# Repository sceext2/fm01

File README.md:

<!-- lang: zh_CN -->
<!-- fm01-2020/fm01_doc -->

# fm01_doc
<https://github.com/fm01-2020/fm01_doc>

胖蚊子 (Fat Mosquito) 系列文档.

胖蚊子系列起源于胖蚊子 1 号 (FM01) 小飞机, 但在制造小飞机的过程中,
相关技术产生了更多项目.
现将所有项目统称为胖蚊子系列, 并将相关文档集中于 `fm01_doc`.

(胖蚊子: 白天休息, 晚上出来嗡嗡嗡 ~ )

注: 目前大部分这些项目都处于起步阶段.

## 已完成的项目

| 代号 (code) | 名称 (name) | 说明 | 成本 (CNY) | 备注 | 完成时间 |
| :--------- | :---------- | :--- | --------: | :--- | :------: |
| [LQFP64-10x10mm-CLAMP](./kicad/lqfp64-10x10mm-clamp) | LQFP64 芯片夹座 | 用于免焊接测试单片机 | 1 | | 2020 |

注: 成本仅供参考.

## 进行中的项目 (2021)

| 代号 (code) | 名称 (name) | 说明 | 成本 (CNY) | 备注 |
| :--------- | :---------- | :--- | --------: | :--- |
| FMUV-2 | 胖蚊子紫外线强度计 | 作为一个精美小礼物 | (100) | |
| FMLHR-1 | 胖蚊子光除毛 | 810nm 近红外光脉冲除毛 | (400) | |
| fmprinter-1 | 胖蚊子打印机 | 简单的廉价小型打印机 | (30) | |
| FMOS-2 | 胖蚊子示波器 FPGA 版 (USB 2.0) | 50Msps 6bit, 30Msps 10bit | (100) | 2022 |
| FMUPS-1 | 胖蚊子电源 | 12V 600W, 降压开关电源, 电池充电器, 逆变器, UPS, 多机并联同步 | (100) | 2022 |
| FMUPS-1-B | FMUPS-1 电池包 | 21700 锂电池, 16.8V, 250W 4h (1kWh) | (500) | 2022 |
| FMSB-1 | 胖蚊子微派 1 | SBC: 全志 A20 SoC | (100) | 2022 |
| FMSB-2 | 胖蚊子微派 2 | SBC: 全志 V3 SoC | (100) | 2022 |
| FMSB-3 | 胖蚊子微派 3 | SBC: 全志 V3s SoC | (100) | 2022 |

注: 成本仅供参考.

## 重要目录

| 目录 | 说明 |
| :--: | :-- |
| [kicad](./kicad) | 胖蚊子系列 PCB |
| [fmp](./fmp) | 胖蚊子系列使用的通信协议 (protocol) |
| [libfm-rs](./libfm-rs) | 胖蚊子系列软件库: 胖蚊子系列是软硬件混合的项目, 硬件需要软件的驱动 |

## 胖蚊子系列设计原则 (6)

+ **廉价**.

  在设计性能可以接受的情况下 (不追求高性能), 尽可能使用廉价的设计与硬件选型, 避免使用昂贵的模块, 组件, 芯片, 元器件.
  追求胖蚊子系列整体的硬件低成本.
  避免因为过高的价格, 而阻止更多人尝试胖蚊子系列.

+ **原料易得**.

  胖蚊子系列的硬件模块, 组件, 元器件等的选型, 以及组装所需使用的各种工具, 应使用方便购买, 货源充足的.
  使用常见的标准, 接口.
  避免因为买不到相应的硬件材料, 而阻止更多人尝试胖蚊子系列.

+ **一致性**.

  胖蚊子系列尽可能共用同样的技术, 模块, 接口, 器件选型, 协议, 工具, 使用同样的设计风格.

+ **数字化与安全性**.

  在胖蚊子系列的各硬件模块之间, 各设备之间, 尽量使用数字通信协议, 不使用模拟通信协议.
  通信协议考虑加密, 完整性, 干扰等安全性因素.
  胖蚊子系列的软硬件设计, 考虑冗余, 模块故障或失效的处理, 应急策略等多种安全机制.
  尽可能避免或减少机器伤人.

  胖蚊子系列的软件部分, 尽可能避免或减少使用 C 语言.
  尽量使用 [rust](https://www.rust-lang.org/) 编程语言, 以提高软件部分的稳定性与安全性.

+ **开源**.

  胖蚊子系列的所有软件代码与硬件设计全部开源, 并尽可能丰富文档内容.
  以便更多人尝试胖蚊子系列.

+ **高级用户界面与机器接口相分离**.

  胖蚊子系列的 **高级用户界面** (图形, 数字, 复杂操作控制, 多媒体等) 全部位于上位机 (PC 或手机).
  MCU 不涉及高级用户界面, 只提供上位机接口 (fmp).

  机器本身 (MCU 侧) 最多只有非常简单的 **低级用户界面** (电源开关, 状态指示灯, 急停按钮).

  尽量分离用户界面和机器接口, 可以方便机器之间的互联协调配合.
  尽量使用机器去控制机器, 把人解放出来.

## LICENSE

[`CC-BY-SA 4.0+`](https://creativecommons.org/licenses/by-sa/4.0/)

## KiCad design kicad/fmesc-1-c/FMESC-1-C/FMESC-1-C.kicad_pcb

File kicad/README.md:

# fm01_doc/kicad
胖蚊子系列 PCB, 使用设计工具 [KiCad](https://kicad-pcb.org/).

## 经过测试验证的电路板

这些 PCB 经过制造, 并测试成功, 达到了设计的预期效果.

| 序号 | 名称 | 说明 | 规格 | 建议颜色 | 版本号 | 成本 (CNY) | 备注 |
| :--: | :-- | :--- | :--- | :-----: | :---- | ---------: | :-- |
| 1 | [`LQFP64-10x10mm-CLAMP`](./lqfp64-10x10mm-clamp) | LQFP64, LQFP48 芯片夹座, 用于免焊接烧录单片机 | 25x25mm 大小 (x3), 1.6mm 厚度, 2 层, FR-4 | 绿 | v0.1 2020-11-15 | 1.0 | |

注: 成本仅供参考.

## 设计中的电路板

这些 PCB 还没有通过测试, 或者还没有制造过, 或者还在设计中.

| 序号 | 名称 | 说明 | 规格 | 建议颜色 | 版本号 | 成本 (CNY) | 备注 |
| :--: | :-- | :--- | :--- | :-----: | :---- | ---------: | :-- |
| 1 | FMPCBVDL-1 | PCB 垂直连接器 (2P, 1.4x2.8mm) | 4x16mm 大小, 1.6mm 厚度, 2 层, FR-4 | 黄 | v0.1 2020-11-29 | 1 | |
| 2 | `FMESC-1-A` | 胖蚊子电调 (FMESC-1) 底层大板 | 48x48mm (48x54mm) 大小, 1.6mm 厚度, 1 层, 铝基 或 FR-4, 24x48mm (M2) 孔距 | 黄 (FR-4), 白 (铝基) | v0.3 2020-11-29 | 18 | |
| 3 | FMESC-1-C | 胖蚊子电调 (FMESC-1) MOS 驱动小板 | 12x20mm 大小, 1.0mm 厚度, 2 层, FR-4 | 蓝 | | 4 | |
| 4 | FMSMD-2 | 步进电机驱动 (4 路), 使用 HR8833MTE (1.5A, 2 细分) | 20x50mm 大小, 1.6mm 厚度, 2 层, FR-4 | 黄 | | 10 | |

## 计划中及设计早期的电路板

这些 PCB 还在设计早期阶段, 或者只是计划中.

| 序号 | 名称 | 说明 | 规格 | 建议颜色 | 版本号 | 成本 (CNY) | 备注 |
| :--: | :-- | :--- | :--- | :-----: | :---- | ---------: | :-- |
| 1 | FMC-1-SF0RC | 胖蚊子主控板 (stm32f030rct6 芯片) | 20x40mm 大小, 1.0mm 厚度, 2 层, FR-4 | 绿 | | 10 | |
| 2 | FMC-1-SF1RE | 胖蚊子主控板 (stm32f103ret6 芯片) | 20x40mm 大小, 1.0mm 厚度, 2 层, FR-4 | 绿 | | 10 | |
| 3 | FM02-B-1 | 胖蚊子 2 号 (FM02) 机架及主要电路板 | 100x100mm 大小, 1.6mm 厚度, 2 层, FR-4 | 黄 | | 10 | |
| 4 | FM01-ES2-1 | 胖蚊子 1 号 (FM01) 承载 esp32-s2 wrover-i 模块的小板 | 20x32mm 大小, 1.0mm 厚度, 2 层, FR-4 | 绿 | | | |

## 胖蚊子系列 PCB 阻焊颜色使用说明

可选颜色 (JLC): `绿`, `红`, `黄`, `蓝`, `白`, `黑` (6 种).

保留颜色 (尽量不使用): `红`, `黑` (2 种).

1. **普通板** (未分类, 默认颜色): `绿` (FR-4, 厚 1.6mm, 1.0mm).

  比如: `LQFP64-10x10mm-CLAMP`

2. **主控板** (单片机 stm32, esp32 等): `绿` (FR-4, 厚 1.0mm).

  比如: `FMC-1-SF0RC`, `FMC-1-SF1RE`, `FM01-ES2-1`

3. **功率板** (电机驱动板, 电源板), **机架**: `黄` (FR-4, 厚 1.6mm).

  比如: `FMESC-1-A`, `FMSMD-2`, `FM02-B-1`

4. **铝基板**: `白` (铝基, 厚 1.6mm, 1.0mm).

5. **特殊板** (飞线板, 4 层板): `蓝` (FR-4, 厚 1.0mm).

  比如: `FMESC-1-C`

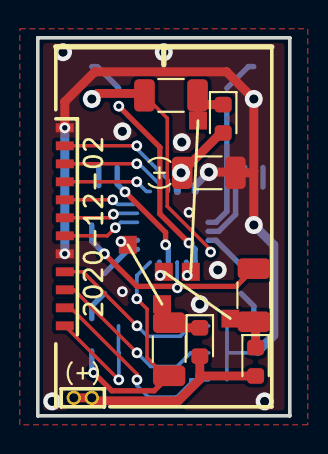
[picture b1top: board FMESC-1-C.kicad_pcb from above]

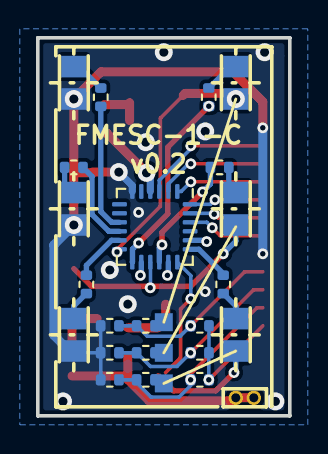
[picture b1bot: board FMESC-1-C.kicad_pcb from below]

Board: 2 copper layers, 14.0 x 21.0 mm, 40 parts (25 on the bottom side), 36 nets.

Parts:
C0, C1, C2, C3: 10u; C_1206_3216Metric
D1, D2, D3: D; D_0603_1608Metric
J1, J2, J3, J4, J5, J6: Conn_01x02; FMPCBVDL-1-S
JA2: Conn_01x01; JS_1P_1x1mm
JB2: Conn_01x01; JS_1P_1x1mm
JC2: Conn_01x01; JS_1P_1x1mm
JM1: Conn_01x12; JS_12P_1.0mm
JP1: Conn_01x02; JT_2P_1.0mm
JV1, JV2, JV3, JV4, JV5, JV6: Conn_01x01; JS_1P_1x1mm
R1, R2, R3, R4, R5, R6: 10; R_0402_1005Metric
R11, R13, R15, R21, R22, R23: 2k; R_0402_1005Metric
R12, R14, R16: 20k; R_0402_1005Metric
U1: FD6288Q; QFN-24-1EP_4x4mm_P0.5mm_EP2.7x2.7mm_nopad

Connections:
+BATT: C0.2, D1.2, D2.2, D3.2, JP1.1, JP1.2, U1.4
/A1: C1.2, J2.1, U1.18
/AHG: R2.1, U1.19
/ALG: R1.1, U1.11
/B1: C2.2, J4.1, U1.15
/BHG: R4.1, U1.16
/BLG: R3.1, U1.10
/C1: C3.2, J6.1, U1.12
/CHG: R6.1, U1.13
/CLG: R5.1, U1.9
/GHA: JM1.7, U1.22
/GHB: JM1.6, U1.23
/GHC: JM1.5, U1.24
/GLA: JM1.4, U1.1
/GLB: JM1.3, U1.2
/GLC: JM1.2, U1.3
/S0: JM1.12, R21.1, R22.1, R23.1
/SA: JM1.11, R11.2, R12.1, R21.2
/SB: JM1.10, R13.2, R14.1, R22.2
/SC: JM1.9, R15.2, R16.1, R23.2
GND: C0.1, J1.1, J3.1, J5.1, JM1.1, JM1.8, R11.1, R13.1, R15.1, U1.6
unnamed: C1.1, D1.1, JV2.1
unnamed: C2.1, D2.1, JV4.1
unnamed: C3.1, D3.1, JV6.1
unnamed: J1.2, R1.2
unnamed: J2.2, R2.2
unnamed: J3.2, R3.2
unnamed: J4.2, R4.2
unnamed: J5.2, R5.2
unnamed: J6.2, R6.2
unnamed: JA2.1, R12.2
unnamed: JB2.1, R14.2
unnamed: JC2.1, R16.2
unnamed: JV1.1, U1.20
unnamed: JV3.1, U1.17
unnamed: JV5.1, U1.14

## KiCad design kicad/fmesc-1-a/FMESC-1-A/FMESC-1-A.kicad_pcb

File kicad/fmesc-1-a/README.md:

# FMESC-1-A

胖蚊子电调 (FMESC-1) 底层大版.
与 [FMESC-1-C](../fmesc-1-c/) 以及 `FMC-1` 主控板配合使用.

+ 设计电池电压: 2s ~ 4s  (6.6V ~ 16.8V)

+ 设计最大单路电流: 40A

## PCB 设计参数

| 序号 | 项目 | 数值 |
| :--: | :-- | ---: |
| 1 | PCB 大小 | 48x48mm (48x54mm) |
| 2 | 材质 | 铝基 厚度 1.6mm 铜箔厚度 1oz (35um) |
| 3 | 层数 | 1 (单面) |
| 4 | 最小线宽线距 | 0.16mm (6mil) |
| 5 | 最小过孔内径 | 0.3mm |
| 6 | 最小过孔外径 | 0.6mm |
| 7 | 最小字符高度 | 0.8mm |
| 8 | 最小过孔间距 | 0.4mm |
| 9 | 最小过孔与线间距 | 0.25mm |
| 10 | 最小非金属化槽宽度 | 0.8mm |

推荐加工厂: [捷配](https://www.jiepei.com/)

## 元件清单

| 序号 | 引用 | 型号 | 封装 | 数量 | 价格 (CNY) |
| :--: | :-- | :--- | :--: | --: | ---------: |
| 1 | `Q1`, `Q2`, `Q3`, `Q4`, `Q5`, `Q6`, `Q7`, `Q8`, `Q9`, `Q10`, `Q11`, `Q12`, `Q13`, `Q14`, `Q15`, `Q16`, `Q17`, `Q18`, `Q19`, `Q20`, `Q21`, `Q22`, `Q23`, `Q24` | AON6504 (NMOS 30V 85A 3.2mR) | DFN5x6 (6x5mm) | 24 | 0.7 x24 = 16.8 |
| 2 | `J1`, `J2`, `J3`, `J4`, `J5`, `J6`, `J7`, `J8`, `J9`, `J10`, `J11`, `J12`, `J13`, `J14`, `J15`, `J16`, `J17`, `J18`, `J19`, `J20`, `J21`, `J22`, `J23`, `J24`, `JT1`, `JT2`, `JT3` | FMPCBVDL-1 (2P, 1.4x2.8mm) | SMD | 27 | 1 |
| 总计 | 31 | 2 | 2 | 31 | 17.8 |

不在电路板上的额外元器件如下:

| 序号 | 型号 | 说明 | 数量 | 价格 (CNY) |
| :--: | :-- | :--- | ---: | ---------: |
| 1 | 电容 50V 470uF 铝电解 直插 | 并接在电源线入口处, 用于维持电调供电电压稳定 | 1 | 0.26 |
| 2 | 二极管 20A 1000V 直插 | (电路保护) 反向并接在电源线入口处, 用于防止电源正负极反接 | 1 | 0.4 |
| 3 | 压敏电阻 20D220K 22V 直插 | (电路保护) 并接在电源线入口处, 用于防止输入过高电压 | 1 | 0.68 |
| 总计 | 3 | | 3 | 1.4 |

注: 价格仅供参考.

## 接口引脚说明

| 序号 | 引用 | 说明 |
| :--: | :-- | :--- |
| 1 | `JG0`, `JG1` ~ `JG12` | GND 接电源负极 |
| 2 | `JB0`, `JB1` ~ `JB12` | VB 接电源正极 |
| 3 | `MA1`, `MB1`, `MC1` | 接 1 号无刷电机 |
| 4 | `MA2`, `MB2`, `MC2` | 接 2 号无刷电机 |
| 5 | `MA3`, `MB3`, `MC3` | 接 3 号无刷电机 |
| 6 | `MA4`, `MB4`, `MC4` | 接 4 号无刷电机 |
| 7 | `J1` ~ `J24` | 接上层电路板 `FMESC-1-C` |
| 8 | `JT1`, `JT2`, `JT3` | 接上层电路板 `FMC-1` |

## 功能电路

TODO

## 保护电路

胖蚊子小飞机整体电路保护方案请见 [电路保护](../../fm01/circuit_protect.md) 文档.

作为四合一电调, 胖蚊子电调 (`FMESC-1-A` 电路板) 在此处充当了主分电板的角色.
因此在电源入口处, 反向并接一只大电流大功率二极管, 用于防止电源正负极反接.
同时并接一只 22V 压敏电阻, 用于过压保护, 防止接入超过最大设计电压的电源.

注意在此种保护机制下, 如果发生电源接错 (反接, 过压) 则本电路板相当于直接短路, 会造成电源承担很大的电流.
此处的保护机制目的是保护本电路板, 以及其余的上级电路板 (比如飞控), 而不是保护电源.

因此, 此处的保护机制单独无法提供足够的安全性, 接入本电路板的电池组, 必须自身具有一定的保护机制, 能够对短路大电流做出反应.
建议的电池组保护机制, 详见上述 *电路保护* 文档, 即采用过流保护 (自恢复保险丝) 以及电池电源指示灯 (故障状态指示).

## 电路板装配说明

完整的 胖蚊子电调 (FMESC-1) 包含的电路板如下:

| 序号 | 名称 | 说明 | 大小 | 材质 | 数量 | 价格 (CNY) |
| :--: | :-- | :--- | ---: | :--- | --: | ---------: |
| 1 | `FMESC-1-A` | 承载 MOS 管的底层大板 | 48x48mm (48x54mm) | 铝基 (或 FR-4) 厚度 1.6mm | 1 | 17.8 |
| 2 | `FMESC-1-C` | MOS 驱动小板 | 12x20mm | FR-4 厚度 1.0mm | 4 | 3.1 x4 = 12.4 |
| 3 | `FMC-1` | 胖蚊子主控板 | 20x40mm | FR-4 厚度 1.0mm | 1 | 10 ? |
| 总计 | 3 | | | 2 | 6 | 40 ? |

注: 价格仅供参考.

胖蚊子电调 装配后为二层结构, 底层为 `FMESC-1-A`, 原件全部采用贴片方式安装.
`FMESC-1-A` 通过 `FMPCBVDL-1` 连接器, 与上层的 `FMESC-1-C` 和 `FMC-1` 小板相连.
上层小板直接插接至底层大板.  上下板间距约 5mm.
最后 `FMESC-1-C` 和 `FMC-1` 的控制信号通过顶层表面的跳线连接.

## 电路板制造历史

| 序号 | 版本号 | 材质 | 阻焊颜色 | 生产文件 | 工厂 | 数量 | 测试结果 | 备注 |
| :--: | :---- | :--- | :-----: | :-----: | :--: | --: | :------ | :--- |
| 1 | `FMESC-1-A v0.2` 2020-11-10 | FR-4 厚度 1.6mm | 绿 | [`6ad8cd0`](https://github.com/sceext2/fm01/tree/6ad8cd0d3cc3d302504e62683a5e1323266cda7f/doc/kicad/fmesc-1-a/dist) | [嘉立创](https://www.jlc.com/) | 5 | 失败 (等待 v0.3) | 第一次制造 |

(2020-11-12)

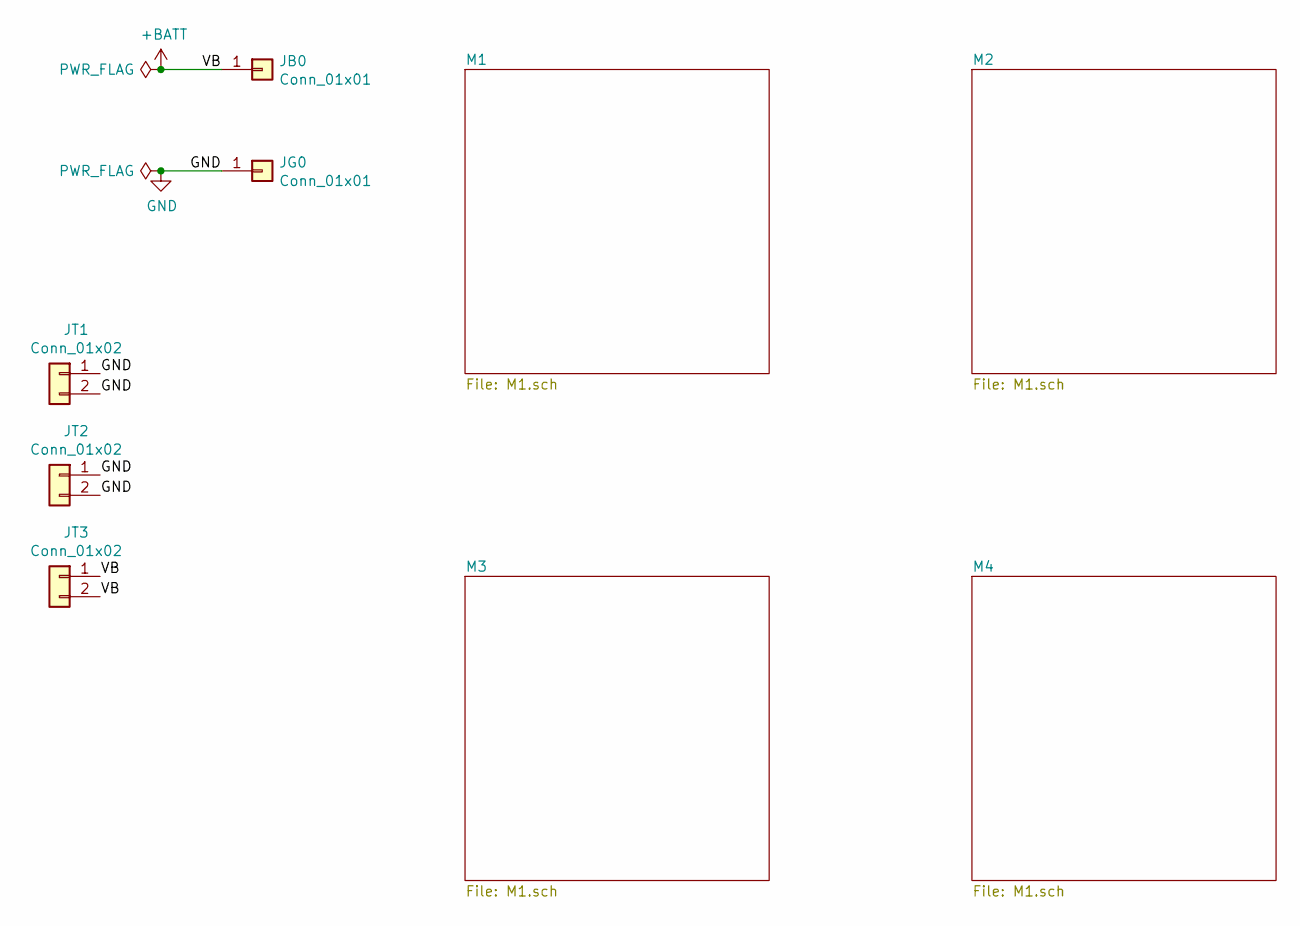
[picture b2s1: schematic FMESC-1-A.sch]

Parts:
JB0: Conn_01x01; JS-JB0
JG0: Conn_01x01; JS-JG0
JT1, JT2, JT3: Conn_01x02; FMPCBVDL-1-S

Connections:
+BATT: JB0.1, JT3.1, JT3.2; also elsewhere on the board
GND: JG0.1, JT1.1, JT1.2, JT2.1, JT2.2; also elsewhere on the board

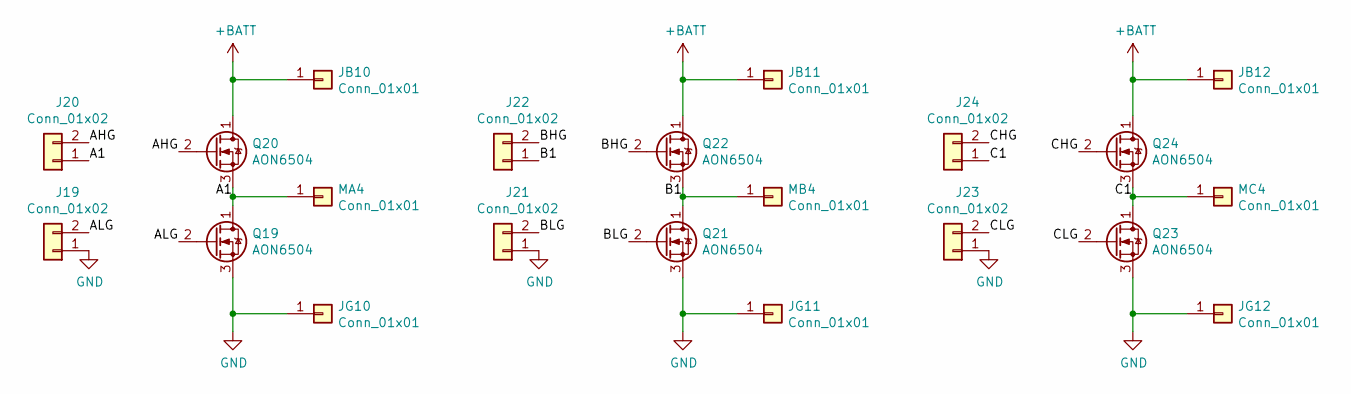
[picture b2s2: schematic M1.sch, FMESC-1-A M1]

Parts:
J1, J2, J3, J4, J5, J6: Conn_01x02; FMPCBVDL-1-S
JB1, JB2, JB3: Conn_01x01; JS-JBx
JG1, JG2, JG3: Conn_01x01; JS-JGx
MA1: Conn_01x01; JS-Jx
MB1: Conn_01x01; JS-Jx
MC1: Conn_01x01; JS-Jx
Q1, Q2, Q3, Q4, Q5, Q6: AON6504; DFN5x6_8L_EP1_P

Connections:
+BATT: JB1.1, JB2.1, JB3.1, Q2.1 (D), Q4.1 (D), Q6.1 (D); also elsewhere on the board
/M1/A1: J2.1, MA1.1, Q1.1 (D), Q2.3 (S)
/M1/AHG: J2.2, Q2.2 (G)
/M1/ALG: J1.2, Q1.2 (G)
/M1/B1: J4.1, MB1.1, Q3.1 (D), Q4.3 (S)
/M1/BHG: J4.2, Q4.2 (G)
/M1/BLG: J3.2, Q3.2 (G)
/M1/C1: J6.1, MC1.1, Q5.1 (D), Q6.3 (S)
/M1/CHG: J6.2, Q6.2 (G)
/M1/CLG: J5.2, Q5.2 (G)
GND: J1.1, J3.1, J5.1, JG1.1, JG2.1, JG3.1, Q1.3 (S), Q3.3 (S), Q5.3 (S); also elsewhere on the board

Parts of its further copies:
J7, J8, J9, J10, J11, J12, J13, J14, J15, J16, J17, J18, J19, J20, J21, J22, J23, J24: Conn_01x02; FMPCBVDL-1-S
JB4, JB5, JB6, JB7, JB8, JB9, JB10, JB11, JB12: Conn_01x01; JS-JBx
JG4, JG5, JG6, JG7, JG8, JG9, JG10, JG11, JG12: Conn_01x01; JS-JGx
MA2, MA3, MA4: Conn_01x01; JS-Jx
MB2, MB3, MB4: Conn_01x01; JS-Jx
MC2, MC3, MC4: Conn_01x01; JS-Jx
Q7, Q8, Q9, Q10, Q11, Q12, Q13, Q14, Q15, Q16, Q17, Q18, Q19, Q20, Q21, Q22, Q23, Q24: AON6504; DFN5x6_8L_EP1_P

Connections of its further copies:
+BATT: JB4.1, JB5.1, JB6.1, JB7.1, JB8.1, JB9.1, JB10.1, JB11.1, JB12.1, Q8.1 (D), Q10.1 (D), Q12.1 (D), Q14.1 (D), Q16.1 (D), Q18.1 (D), Q20.1 (D), Q22.1 (D), Q24.1 (D); also elsewhere on the board
/M2/A1: J8.1, MA2.1, Q7.1 (D), Q8.3 (S)
/M2/AHG: J8.2, Q8.2 (G)
/M2/ALG: J7.2, Q7.2 (G)
/M2/B1: J10.1, MB2.1, Q9.1 (D), Q10.3 (S)
/M2/BHG: J10.2, Q10.2 (G)
/M2/BLG: J9.2, Q9.2 (G)
/M2/C1: J12.1, MC2.1, Q11.1 (D), Q12.3 (S)
/M2/CHG: J12.2, Q12.2 (G)
/M2/CLG: J11.2, Q11.2 (G)
/M3/A1: J14.1, MA3.1, Q13.1 (D), Q14.3 (S)
/M3/AHG: J14.2, Q14.2 (G)
/M3/ALG: J13.2, Q13.2 (G)
/M3/B1: J16.1, MB3.1, Q15.1 (D), Q16.3 (S)
/M3/BHG: J16.2, Q16.2 (G)
/M3/BLG: J15.2, Q15.2 (G)
/M3/C1: J18.1, MC3.1, Q17.1 (D), Q18.3 (S)
/M3/CHG: J18.2, Q18.2 (G)
/M3/CLG: J17.2, Q17.2 (G)
/M4/A1: J20.1, MA4.1, Q19.1 (D), Q20.3 (S)
/M4/AHG: J20.2, Q20.2 (G)
/M4/ALG: J19.2, Q19.2 (G)
/M4/B1: J22.1, MB4.1, Q21.1 (D), Q22.3 (S)
/M4/BHG: J22.2, Q22.2 (G)
/M4/BLG: J21.2, Q21.2 (G)
/M4/C1: J24.1, MC4.1, Q23.1 (D), Q24.3 (S)
/M4/CHG: J24.2, Q24.2 (G)
/M4/CLG: J23.2, Q23.2 (G)
GND: J7.1, J9.1, J11.1, J13.1, J15.1, J17.1, J19.1, J21.1, J23.1, JG4.1, JG5.1, JG6.1, JG7.1, JG8.1, JG9.1, JG10.1, JG11.1, JG12.1, Q7.3 (S), Q9.3 (S), Q11.3 (S), Q13.3 (S), Q15.3 (S), Q17.3 (S), Q19.3 (S), Q21.3 (S), Q23.3 (S); also elsewhere on the board

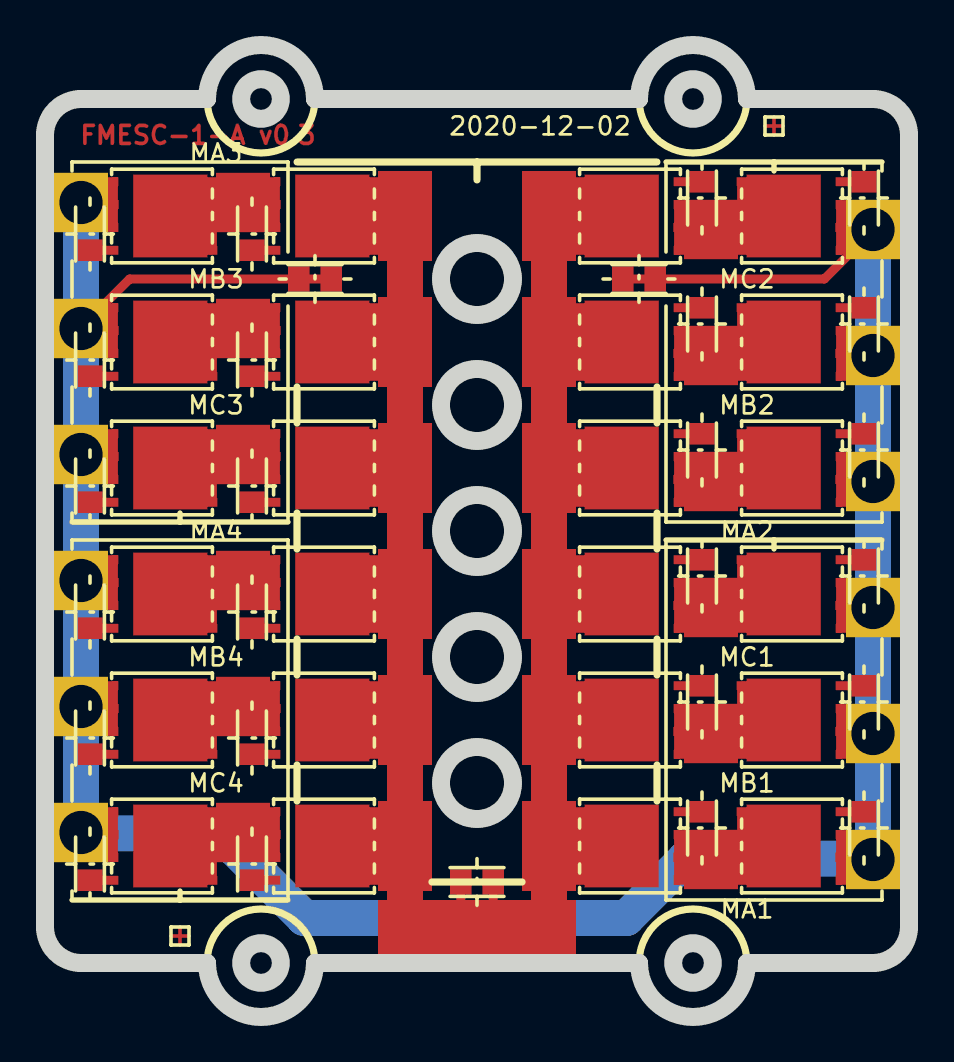
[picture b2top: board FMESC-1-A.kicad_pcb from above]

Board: 2 copper layers, 48.0 x 54.0 mm, 89 parts (1 on the bottom side), 38 nets.

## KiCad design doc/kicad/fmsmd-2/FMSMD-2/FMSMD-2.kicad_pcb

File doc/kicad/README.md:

# doc/kicad
胖蚊子系列 PCB, 使用设计工具 [KiCad](https://kicad-pcb.org/).

## 经过测试验证的电路板

这些 PCB 经过制造, 并测试成功, 达到了设计的预期效果.

| 序号 | 名称 | 说明 | 规格 | 建议颜色 | 版本号 | 成本 (CNY) | 备注 |
| :--: | :-- | :--- | :--- | :-----: | :---- | ---------: | :-- |
| 1 | [`LQFP64-10x10mm-CLAMP`](./lqfp64-10x10mm-clamp) | LQFP64, LQFP48 芯片夹座, 用于免焊接烧录单片机 | 25x25mm 大小 (x3), 1.6mm 厚度, 2 层, FR-4 | 绿 | v0.1 2020-11-15 | 1.0 | |

注: 成本仅供参考.

## 设计中的电路板

这些 PCB 还没有通过测试, 或者还没有制造过, 或者还在设计中.

| 序号 | 名称 | 说明 | 规格 | 建议颜色 | 版本号 | 成本 (CNY) | 备注 |
| :--: | :-- | :--- | :--- | :-----: | :---- | ---------: | :-- |
| 1 | FMPCBVDL-1 | PCB 垂直连接器 (2P, 1.4x2.8mm) | 4x16mm 大小, 1.6mm 厚度, 2 层, FR-4 | 黄 | v0.1 2020-11-29 | 1 | |
| 2 | `FMESC-1-A` | 胖蚊子电调 (FMESC-1) 底层大板 | 48x48mm (48x54mm) 大小, 1.6mm 厚度, 1 层, 铝基 或 FR-4, 24x48mm (M2) 孔距 | 黄 (FR-4), 白 (铝基) | v0.3 2020-11-29 | 18 | |
| 3 | FMESC-1-C | 胖蚊子电调 (FMESC-1) MOS 驱动小板 | 12x20mm 大小, 1.0mm 厚度, 2 层, FR-4 | 蓝 | | 4 | |
| 4 | FMSMD-2 | 步进电机驱动 (4 路), 使用 HR8833 | 20x50mm 大小, 1.6mm 厚度, 2 层, FR-4 | 黄 | | 10 | |

## 计划中及设计早期的电路板

这些 PCB 还在设计早期阶段, 或者只是计划中.

| 序号 | 名称 | 说明 | 规格 | 建议颜色 | 版本号 | 成本 (CNY) | 备注 |
| :--: | :-- | :--- | :--- | :-----: | :---- | ---------: | :-- |
| 1 | FMC-1-SF0RC | 胖蚊子主控板 (stm32f030rct6 芯片) | 20x40mm 大小, 1.0mm 厚度, 2 层, FR-4 | 绿 | | 10 | |
| 2 | FMC-1-SF1RE | 胖蚊子主控板 (stm32f103ret6 芯片) | 20x40mm 大小, 1.0mm 厚度, 2 层, FR-4 | 绿 | | 10 | |
| 3 | FM02-B-1 | 胖蚊子 2 号 (FM02) 机架及主要电路板 | 100x100mm 大小, 1.6mm 厚度, 2 层, FR-4 | 黄 | | 10 | |
| 4 | FM01-ES2-1 | 胖蚊子 1 号 (FM01) 承载 esp32-s2 wrover-i 模块的小板 | 20x32mm 大小, 1.0mm 厚度, 2 层, FR-4 | 绿 | | | |

## 胖蚊子系列 PCB 阻焊颜色使用说明

可选颜色 (JLC): `绿`, `红`, `黄`, `蓝`, `白`, `黑` (6 种).

保留颜色 (尽量不使用): `红`, `黑` (2 种).

1. **普通板** (未分类, 默认颜色): `绿` (FR-4, 厚 1.6mm, 1.0mm).

  比如: `LQFP64-10x10mm-CLAMP`

2. **主控板** (单片机 stm32, esp32 等): `绿` (FR-4, 厚 1.0mm).

  比如: `FMC-1-SF0RC`, `FMC-1-SF1RE`, `FM01-ES2-1`

3. **功率板** (电机驱动板, 电源板), **机架**: `黄` (FR-4, 厚 1.6mm).

  比如: `FMESC-1-A`, `FMSMD-2`, `FM02-B-1`

4. **铝基板**: `白` (铝基, 厚 1.6mm, 1.0mm).

5. **特殊板** (飞线板, 4 层板): `蓝` (FR-4, 厚 1.0mm).

  比如: `FMESC-1-C`

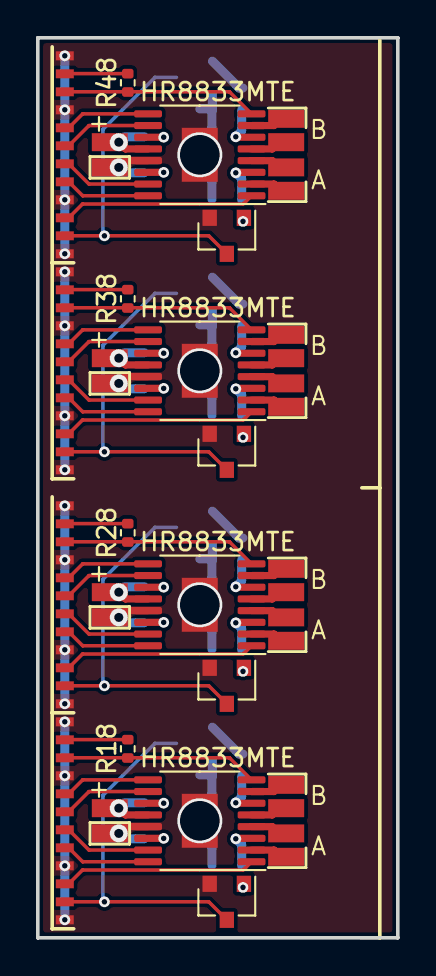
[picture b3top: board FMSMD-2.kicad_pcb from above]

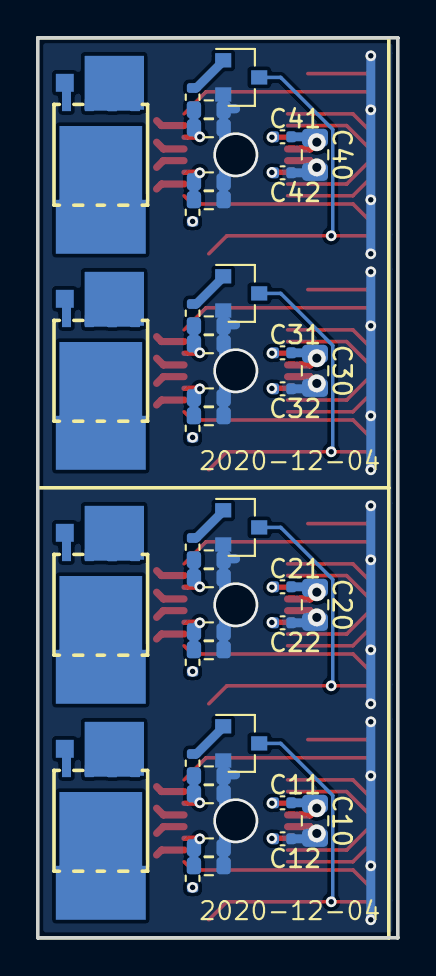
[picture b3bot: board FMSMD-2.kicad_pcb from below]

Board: 2 copper layers, 20.0 x 50.0 mm, 96 parts (56 on the bottom side), 89 nets.

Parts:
C10, C20, C30, C40: 10u; C_0805_2012Metric
C11, C21, C31, C41: 10n; C_0402_1005Metric
C12, C22, C32, C42: 2.2u; C_0402_1005Metric
JAO11, JAO12, JAO21, JAO22, JAO31, JAO32, JAO41, JAO42: Conn_01x01; JS-1x2mm
JBO11, JBO12, JBO21, JBO22, JBO31, JBO32, JBO41, JBO42: Conn_01x01; JS-1x2mm
JC1, JC2, JC3, JC4: Conn_01x12; JS_12P_1.0mm
JG1, JG2, JG3, JG4: Conn_01x01; JS-1x2mm
JQD1, JQD2, JQD3, JQD4: Conn_01x01; JS-Jx
JQG1, JQG2, JQG3, JQG4: Conn_01x01; JS-1x1mm
JQS1, JQS2, JQS3, JQS4: Conn_01x01; JS-JBx
JVM1, JVM2, JVM3, JVM4: Conn_01x01; JS-1x2mm
Q1, Q2, Q3, Q4: AON6504; DFN5x6_8L_EP1_P
Q11, Q12, Q21, Q22, Q31, Q32, Q41, Q42: AO3422; SOT-23
R11, R12, R13, R14, R21, R22, R23, R24, R31, R32, R33, R34, R41, R42, R43, R44: 0; R_0603_1608Metric
R15, R16, R25, R26, R35, R36, R45, R46: 0; R_0402_1005Metric
R18, R28, R38, R48: 10k; R_0402_1005Metric
U1, U2, U3, U4: HR8833MTE; HTSSOP-16-1EP_4.4x5mm_P0.65mm_EP3x3mm

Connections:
/M1/3V3: JC1.11, R18.2
/M1/A1: JC1.5, U1.16
/M1/A2: JC1.6, U1.15
/M1/AIS: R11.1, R13.1, R15.1, U1.3
/M1/AO1: JAO11.1, U1.2
/M1/AO2: JAO12.1, U1.4
/M1/B1: JC1.8, U1.9
/M1/B2: JC1.7, U1.10
/M1/BIS: R12.1, R14.1, R16.2, U1.6
/M1/BO1: JBO11.1, U1.7
/M1/BO2: JBO12.1, U1.5
/M1/NFAULT: JC1.10, R18.1, U1.8
/M1/NSLEEP: JC1.3, U1.1
/M1/VIS: JC1.2, Q11.3, Q12.3
/M1/VM: C10.1, C11.1, JVM1.1, U1.12
/M2/3V3: JC2.11, R28.2
/M2/A1: JC2.5, U2.16
/M2/A2: JC2.6, U2.15
/M2/AIS: R21.1, R23.1, R25.1, U2.3
/M2/AO1: JAO21.1, U2.2
/M2/AO2: JAO22.1, U2.4
/M2/B1: JC2.8, U2.9
/M2/B2: JC2.7, U2.10
/M2/BIS: R22.1, R24.1, R26.2, U2.6
/M2/BO1: JBO21.1, U2.7
/M2/BO2: JBO22.1, U2.5
/M2/NFAULT: JC2.10, R28.1, U2.8
/M2/NSLEEP: JC2.3, U2.1
/M2/VIS: JC2.2, Q21.3, Q22.3
/M2/VM: C20.1, C21.1, JVM2.1, U2.12
/M3/3V3: JC3.11, R38.2
/M3/A1: JC3.5, U3.16
/M3/A2: JC3.6, U3.15
/M3/AIS: R31.1, R33.1, R35.1, U3.3
/M3/AO1: JAO31.1, U3.2
/M3/AO2: JAO32.1, U3.4
/M3/B1: JC3.8, U3.9
/M3/B2: JC3.7, U3.10
/M3/BIS: R32.1, R34.1, R36.2, U3.6
/M3/BO1: JBO31.1, U3.7
/M3/BO2: JBO32.1, U3.5
/M3/NFAULT: JC3.10, R38.1, U3.8
/M3/NSLEEP: JC3.3, U3.1
/M3/VIS: JC3.2, Q31.3, Q32.3
/M3/VM: C30.1, C31.1, JVM3.1, U3.12
/M4/3V3: JC4.11, R48.2
/M4/A1: JC4.5, U4.16
/M4/A2: JC4.6, U4.15
/M4/AIS: R41.1, R43.1, R45.1, U4.3
/M4/AO1: JAO41.1, U4.2
/M4/AO2: JAO42.1, U4.4
/M4/B1: JC4.8, U4.9
/M4/B2: JC4.7, U4.10
/M4/BIS: R42.1, R44.1, R46.2, U4.6
/M4/BO1: JBO41.1, U4.7
/M4/BO2: JBO42.1, U4.5
/M4/NFAULT: JC4.10, R48.1, U4.8
/M4/NSLEEP: JC4.3, U4.1
/M4/VIS: JC4.2, Q41.3, Q42.3
/M4/VM: C40.1, C41.1, JVM4.1, U4.12
GND: C10.2, C12.1, C20.2, C22.1, C30.2, C32.1, C40.2, C42.1, JC1.1, JC1.4, JC1.9, JC1.12, JC2.1, JC2.4, JC2.9, JC2.12, JC3.1, JC3.4, JC3.9, JC3.12, JC4.1, JC4.4, JC4.9, JC4.12, JG1.1, JG2.1, JG3.1, JG4.1, Q11.2, Q12.2, Q21.2, Q22.2, Q31.2, Q32.2, Q41.2, Q42.2, R11.2, R12.2, R13.2, R14.2, R21.2, R22.2, R23.2, R24.2, R31.2, R32.2, R33.2, R34.2, R41.2, R42.2, R43.2, R44.2, U1.13, U1.17, U2.13, U2.17, U3.13, U3.17, U4.13, U4.17
unnamed: C11.2, U1.11
unnamed: C12.2, U1.14
unnamed: C21.2, U2.11
unnamed: C22.2, U2.14
unnamed: C31.2, U3.11
unnamed: C32.2, U3.14
unnamed: C41.2, U4.11
unnamed: C42.2, U4.14
unnamed: JQD1.1, Q1.1
unnamed: JQD2.1, Q2.1
unnamed: JQD3.1, Q3.1
unnamed: JQD4.1, Q4.1
unnamed: JQG1.1, Q1.3
unnamed: JQG2.1, Q2.3
unnamed: JQG3.1, Q3.3
unnamed: JQG4.1, Q4.3
unnamed: JQS1.1, Q1.2
unnamed: JQS2.1, Q2.2
unnamed: JQS3.1, Q3.2
unnamed: JQS4.1, Q4.2
unnamed: Q11.1, R15.2
unnamed: Q12.1, R16.1
unnamed: Q21.1, R25.2
unnamed: Q22.1, R26.1
unnamed: Q31.1, R35.2
unnamed: Q32.1, R36.1
unnamed: Q41.1, R45.2
unnamed: Q42.1, R46.1

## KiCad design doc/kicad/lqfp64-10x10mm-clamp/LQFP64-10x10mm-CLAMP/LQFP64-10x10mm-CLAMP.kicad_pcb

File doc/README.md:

<!-- lang: zh_CN -->
<!-- fm01/doc/ -->

# fm01/doc
<https://github.com/sceext2/fm01/tree/main/doc>

胖蚊子 (Fat Mosquito) 系列文档.

胖蚊子系列起源于胖蚊子 1 号 (FM01) 小飞机, 但在制造小飞机的过程中,
相关技术产生了更多项目.
现将所有项目统称为胖蚊子系列, 并将相关文档集中于 `fm01/doc`.

(胖蚊子: 白天休息, 晚上出来嗡嗡嗡 ~ )

注: 目前大部分这些项目都处于起步阶段.

## 胖蚊子系列廉价多轴小飞机

设计中的机型:

| 序号 | 机型 | 说明 | 整机成本 (CNY) | 备注 |
| :--: | :-- | :--- | ------------: | :--- |
| 1 | 胖蚊子 1 号 (FM01) | 600 克重型 3 寸, 胖蚊子飞控, 胖蚊子电调, 机载手机 | 340 | |
| 2 | 胖蚊子 2 号 (FM02) | 廉价 2 寸空心杯, PCB 机架, esp32-cam | 60 | |
| 3 | 胖蚊子 5 号 (FM05) | 10 寸混合 5 轴小飞机, 冗余设计, 全电磁屏蔽, 大气激光通信 | 200 | |

计划中 (尚未开始设计) 的机型:

| 序号 | 机型 | 说明 | 整机成本 (CNY) | 备注 |
| :--: | :-- | :--- | ------------: | :--- |
| 1 | 胖蚊子 3 号 (FM03) | 2 寸小无刷, 防水特性 | | |
| 2 | 胖蚊子 4 号 (FM04) | 双摄像头 3D 视觉 | | |

注: 成本仅供参考.

## 胖蚊子系列小项目

| 名称 | 说明 | 成本 (CNY) | 备注 |
| :-- | :--- | ---------: | :--- |
| 胖蚊子打印机 (fmprinter-1) | 简单的廉价小型打印机 | 30 | |
| 胖蚊子光除毛 (FMLHR-1) | 810nm 近红外光脉冲除毛 | 400 | |
| 胖蚊子示波器 (FMOS-2) | ADC 芯片 + FPGA, USB2.0/USB3.0 接口 (USB2.0 版本 50Msps 6bit / 30Msps 10bit) | 50 | |
| 胖蚊子宽电压双向电源 (FMUPS-1) | 12V 600W, 降压开关电源 + 电池充电器 + 逆变器 + UPS, 支持多机并联同步 | 100 | |
| FMUPS-1 电池包 | 基于 21700 锂电池, 4 串 16.8V, 250W 4h (1kWh) | 500 | FMUPS-1 支持 1 ~ 8 个电池包, 最大 2kW (8kWh) |
| 胖蚊子电调 (FMESC-1) | 4 路无刷无感电机驱动, 16V 40A | 50 | |
| 胖蚊子飞控 (FMFCS) | 用于胖蚊子系列小飞机 | | |

注: 成本仅供参考.

## 胖蚊子系列 PCB

胖蚊子系列使用的电路板.
详见 [kicad](./kicad) 目录.

| 序号 | 名称 | 说明 | 成本 (CNY) | 备注 |
| :--: | :-- | :--- | ---------: | :--- |
| 1 | `LQFP64-10x10mm-CLAMP` | LQFP64 芯片夹座, 用于免焊接烧录单片机 | 1 | 测试成功 |
| 2 | FMSMD-2 | 步进电机驱动 (4 路), HR8833MTE (1.5A, 2 细分) | | |
| 3 | FM02-B-1 | 胖蚊子 2 号 (FM02) 机架及主要电路板 | 10 | |

注: 成本仅供参考.

## 胖蚊子协议

胖蚊子系列使用的通信协议 (protocol).
详见 [fmp](./fmp) 目录.

| 名称 | 说明 | 备注 |
| :-- | :--- | :--- |
| fmp-uart | 胖蚊子串口协议 (数据链路层), 在 UART 的基础上进行简单封装 | |
| fmp-uart-fmesc | 胖蚊子串口协议 (应用层), 用于胖蚊子电调 (FMESC-1) | |
| fmp-uart-fmprinter | 胖蚊子串口协议 (应用层), 用于胖蚊子打印机 (fmprinter-1) | |
| fmp-usb | MCU 与上位机之间 (数据链路层), USB 接口 | |

## 胖蚊子系列软件库

胖蚊子系列是软硬件混合的项目, 硬件需要软件的驱动.
详见 [libfm-rs](./libfm-rs) 目录.

| 名称 | 说明 | 语言 | 运行环境 | 备注 |
| :-- | :--- | :--: | :------ | :--- |
| libfmp.rs | 胖蚊子系列通信协议 (Fat Mosquito Protocol) 的实现和封装, 以及相关安全功能 | rust | arm, x86 | |
| libfmhal.rs | MCU 硬件抽象 (Hardware Abstraction Layer) | rust | stm32f0, stm32f1 | |
| libfmutil.rs | 胖蚊子工具库, 提供可以在多个项目中复用的代码 | rust | arm, x86 | |
| fmprinter-1 | 胖蚊子打印机 (fmprinter-1) 固件 | rust | stm32f0, stm32f1 | |
| fmprinter-ui | 胖蚊子打印机用户界面 | js (electron) | Linux, Android | |
| fmfc | 胖蚊子飞控 (机载部分) | rust, C | esp32, esp32s2, stm32f1 | |

## 胖蚊子系列设计原则 (6)

+ **廉价**.

  在设计性能可以接受的情况下 (不追求高性能), 尽可能使用廉价的设计与硬件选型, 避免使用昂贵的模块, 组件, 芯片, 元器件.
  追求胖蚊子系列整体的硬件低成本.
  避免因为过高的价格, 而阻止更多人尝试胖蚊子系列.

+ **原料易得**.

  胖蚊子系列的硬件模块, 组件, 元器件等的选型, 以及组装所需使用的各种工具, 应使用方便购买, 货源充足的.
  使用常见的标准, 接口.
  避免因为买不到相应的硬件材料, 而阻止更多人尝试胖蚊子系列.

+ **一致性**.

  胖蚊子系列尽可能共用同样的技术, 模块, 接口, 器件选型, 协议, 工具, 使用同样的设计风格.

+ **数字化与安全性**.

  在胖蚊子系列的各硬件模块之间, 各设备之间, 尽量使用数字通信协议, 不使用模拟通信协议.
  通信协议考虑加密, 完整性, 干扰等安全性因素.
  胖蚊子系列的软硬件设计, 考虑冗余, 模块故障或失效的处理, 应急策略等多种安全机制.
  尽可能避免或减少机器伤人.

  胖蚊子系列的软件部分, 尽可能避免或减少使用 C 语言.
  尽量使用 [rust](https://www.rust-lang.org/) 编程语言, 以提高软件部分的稳定性与安全性.

+ **开源**.

  胖蚊子系列的所有软件代码与硬件设计全部开源, 并尽可能丰富文档内容.
  以便更多人尝试胖蚊子系列.

+ **高级用户界面与机器接口相分离**.

  胖蚊子系列的 **高级用户界面** (图形, 数字, 复杂操作控制, 多媒体等) 全部位于上位机 (PC 或手机).
  MCU 不涉及高级用户界面, 只提供上位机接口 (fmp).

  机器本身 (MCU 侧) 最多只有非常简单的 **低级用户界面** (电源开关, 状态指示灯, 急停按钮).

  尽量分离用户界面和机器接口, 可以方便机器之间的互联协调配合.
  尽量使用机器去控制机器, 把人解放出来.

## LICENSE

[`CC-BY-SA 4.0+`](https://creativecommons.org/licenses/by-sa/4.0/)

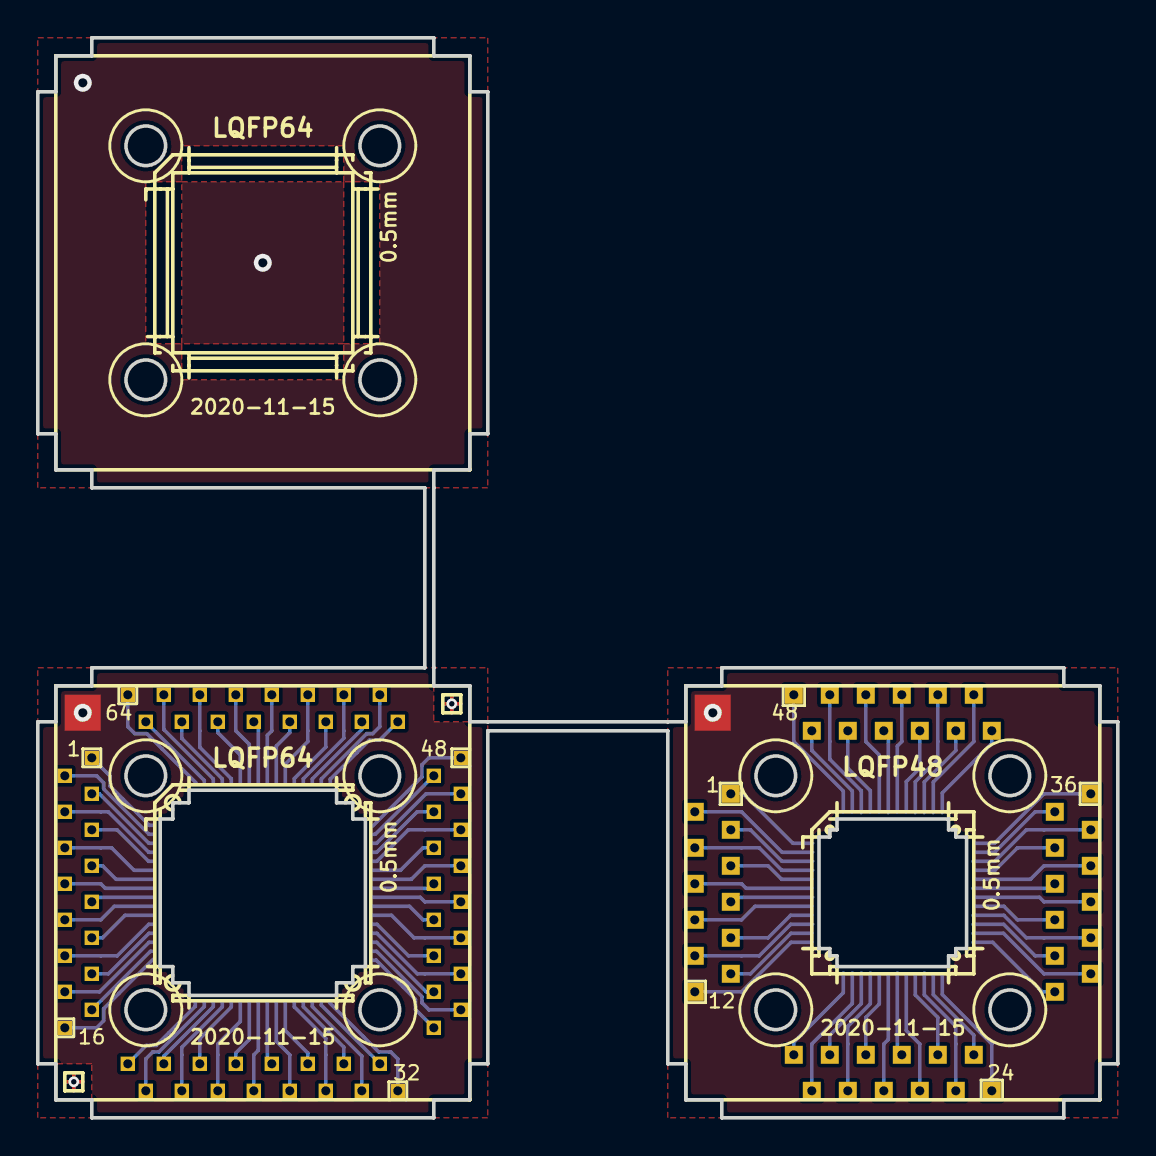
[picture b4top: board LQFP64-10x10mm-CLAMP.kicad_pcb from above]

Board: 2 copper layers, 60.0 x 60.0 mm, 12 parts (0 on the bottom side), 113 nets.

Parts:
J0, J10: Conn_01x01; JS_2x2mm
J1, J2, J3, J4: Conn_01x16; JD_16P_2.0mm
J5, J6, J7, J8: Conn_01x12; JD_12P_2.0mm
U1: LQFP64-G; LQFP-64_10x10mm_P0.5mm_H
U2: LQFP48-G; LQFP-48_7x7mm_P0.5mm_H

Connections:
/P101: J1.1, U1.1
/P102: J1.2, U1.2
/P103: J1.3, U1.3
/P104: J1.4, U1.4
/P105: J1.5, U1.5
/P106: J1.6, U1.6
/P107: J1.7, U1.7
/P108: J1.8, U1.8
/P109: J1.9, U1.9
/P110: J1.10, U1.10
/P111: J1.11, U1.11
/P112: J1.12, U1.12
/P113: J1.13, U1.13
/P114: J1.14, U1.14
/P115: J1.15, U1.15
/P116: J1.16, U1.16
/P117: J2.1, U1.17
/P118: J2.2, U1.18
/P119: J2.3, U1.19
/P120: J2.4, U1.20
/P121: J2.5, U1.21
/P122: J2.6, U1.22
/P123: J2.7, U1.23
/P124: J2.8, U1.24
/P125: J2.9, U1.25
/P126: J2.10, U1.26
/P127: J2.11, U1.27
/P128: J2.12, U1.28
/P129: J2.13, U1.29
/P130: J2.14, U1.30
/P131: J2.15, U1.31
/P132: J2.16, U1.32
/P133: J3.1, U1.33
/P134: J3.2, U1.34
/P135: J3.3, U1.35
/P136: J3.4, U1.36
/P137: J3.5, U1.37
/P138: J3.6, U1.38
/P139: J3.7, U1.39
/P140: J3.8, U1.40
/P141: J3.9, U1.41
/P142: J3.10, U1.42
/P143: J3.11, U1.43
/P144: J3.12, U1.44
/P145: J3.13, U1.45
/P146: J3.14, U1.46
/P147: J3.15, U1.47
/P148: J3.16, U1.48
/P149: J4.1, U1.49
/P150: J4.2, U1.50
/P151: J4.3, U1.51
/P152: J4.4, U1.52
/P153: J4.5, U1.53
/P154: J4.6, U1.54
/P155: J4.7, U1.55
/P156: J4.8, U1.56
/P157: J4.9, U1.57
/P158: J4.10, U1.58
/P159: J4.11, U1.59
/P160: J4.12, U1.60
/P161: J4.13, U1.61
/P162: J4.14, U1.62
/P163: J4.15, U1.63
/P164: J4.16, U1.64
/P201: J5.1, U2.1
/P202: J5.2, U2.2
/P203: J5.3, U2.3
/P204: J5.4, U2.4
/P205: J5.5, U2.5
/P206: J5.6, U2.6
/P207: J5.7, U2.7
/P208: J5.8, U2.8
/P209: J5.9, U2.9
/P210: J5.10, U2.10
/P211: J5.11, U2.11
/P212: J5.12, U2.12
/P213: J6.1, U2.13
/P214: J6.2, U2.14
/P215: J6.3, U2.15
/P216: J6.4, U2.16
/P217: J6.5, U2.17
/P218: J6.6, U2.18
/P219: J6.7, U2.19
/P220: J6.8, U2.20
/P221: J6.9, U2.21
/P222: J6.10, U2.22
/P223: J6.11, U2.23
/P224: J6.12, U2.24
/P225: J7.1, U2.25
/P226: J7.2, U2.26
/P227: J7.3, U2.27
/P228: J7.4, U2.28
/P229: J7.5, U2.29
/P230: J7.6, U2.30
/P231: J7.7, U2.31
/P232: J7.8, U2.32
/P233: J7.9, U2.33
/P234: J7.10, U2.34
/P235: J7.11, U2.35
/P236: J7.12, U2.36
/P237: J8.1, U2.37
/P238: J8.2, U2.38
/P239: J8.3, U2.39
/P240: J8.4, U2.40
/P241: J8.5, U2.41
/P242: J8.6, U2.42
/P243: J8.7, U2.43
/P244: J8.8, U2.44
/P245: J8.9, U2.45
/P246: J8.10, U2.46
/P247: J8.11, U2.47
/P248: J8.12, U2.48
GND: J0.1, J10.1

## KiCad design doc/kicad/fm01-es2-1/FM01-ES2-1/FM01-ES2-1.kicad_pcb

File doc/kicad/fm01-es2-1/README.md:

# FM01-ES2-1

胖蚊子 1 号 (FM01) 用来承载 esp32-s2 wrover-i 模块的 PCB 小板.

## PCB 设计参数

| 序号 | 项目 | 数值 |
| :--: | :-- | ---: |
| 1 | PCB 大小 | 20x32mm |
| 2 | 材质 | FR-4 厚度 1.0mm 铜箔厚度 1oz (35um) |
| 3 | 层数 | 2 (双面) |
| 4 | 最小线宽线距 | 0.16mm (6mil) |
| 5 | 最小过孔内径 | 0.3mm |
| 6 | 最小过孔外径 | 0.6mm |
| 7 | 最小字符高度 | 0.8mm |
| 8 | 最小过孔间距 | 0.4mm |
| 9 | 最小过孔与线间距 | 0.25mm |
| 10 | 最小非金属化槽宽度 | 0.8mm |

推荐加工厂: [捷配](https://www.jiepei.com/)

## 元件清单

| 序号 | 引用 | 型号 | 封装 | 数量 | 价格 (CNY) |
| :--: | :-- | :--- | :--: | --: | ---------: |
| 1 | `U1` | [esp32-s2 wrover-i](https://www.espressif.com/sites/default/files/documentation/esp32-s2-wrover_esp32-s2-wrover-i_datasheet_cn.pdf) (4MB) 模块 | 18x31mm | 1 | 20 |
| 2 | `D1` | 翠绿色 LED (电源指示灯) | SMD 0402 | 1 | 0.04 |
| 3 | `D2` | 冰蓝色 LED (状态指示灯) | SMD 0402 | 1 | 0.08 |
| 4 | `J1` | micro-USB 插座 (连接上位机) | SMD (F2B4) | 1 | 0.09 |
| 5 | `J2`, `J3` | 1.25mm 10P 插座 卧式 | SMD | 2 | 0.34 x2 = 0.68 |
| 6 | `J4` | FFC/FPC 0.5mm 30P 插座 翻盖式 | SMD | 1 | 0.45 |
| 7 | `C1` | 电容 22uF | SMD 钽电容 A型 (3216-18) | 1 | 0.81 |
| 8 | `C2`, `C3`, `C4` | 电容 0.1uF | SMD 0402 | 3 | 0.01 x3 = 0.03 |
| 9 | `C10`, `C11` | 电容 20pF (不上件) | SMD 0402 | 2 | 0.03 x2 |
| 10 | `R1`, `R2` | 电阻 22 | SMD 0402 | 2 | 0.024 x2 = 0.05 |
| 11 | `R3`, `R18`, `R34` | 电阻 10k | SMD 0402 | 3 | 0.024 x3 = 0.08 |
| 12 | `R4`, `R10`, `R11`, `R35`, `R36`, `R53` | 电阻 0 | SMD 0402 | 6 | 0.024 x6 = 0.15 |
| 13 | `R30`, `R31`, `R32`, `R33`, `R50`, `R51`, `R52` | 电阻 1k | SMD 0402 | 7 | 0.024 x7 = 0.17 |
| 总计 | 31 | 13 | 6 | 29 | 20 + 2.62 = 22.62 |

注: 价格仅供参考.

## 接口引脚说明

+ **J1** micro-USB (USB1.1 12Mbps)

  上位机接口, 用于连接 esp32-s2 (作为 USB device) 和上位机 (USB host).

+ **J2** 主要功能连接 (1.25mm 10P)

  | 序号 | 名称 | 说明 |
  | :--: | :-- | :--- |
  | 1 | `3V3` | 3.3V 电源供电 |
  | 2 | `GND` | 接地 |
  | 3 | `IO1` | 引出 esp32-s2 的 `IO1` |
  | 4 | `IO2` | 引出 esp32-s2 的 `IO2` |
  | 5 | `IO3` | 引出 esp32-s2 的 `IO3` |
  | 6 | `IO4` | 引出 esp32-s2 的 `IO4` |
  | 7 | `IO5` | 引出 esp32-s2 的 `IO5` |
  | 8 | `IO6` | 引出 esp32-s2 的 `IO6` |
  | 9 | `IO7` | 引出 esp32-s2 的 `IO7` |
  | 10 | `IO8` | 引出 esp32-s2 的 `IO8` |

+ **J3** 次要功能连接 (1.25mm 10P)

  | 序号 | 名称 | 说明 |
  | :--: | :-- | :--- |
  | 1 | `VI` | 电流传感器电压输入 (用于电流测量功能) |
  | 2 | `GND` | 接地 |
  | 3 | `IO13` | 引出 esp32-s2 的 `IO13`, 与 `J4` 共同引出 |
  | 4 | `IO14` | 引出 esp32-s2 的 `IO14`, 与 `J4` 共同引出 |
  | 5 | `IO15` | 引出 esp32-s2 的 `IO15` |
  | 6 | `IO16` | 引出 esp32-s2 的 `IO16` |
  | 7 | `IO17` | 引出 esp32-s2 的 `IO17` |
  | 8 | `IO18` | 引出 esp32-s2 的 `IO18` (带 10k 上拉电阻) |
  | 9 | `GND` | 接地 |
  | 10 | `VBAT` | 电池电压输入 (用于电池电压测量功能) |

+ **J4** 扩展 (调试) 功能连接 (FFC/FPC 0.5mm 30P)

  | 序号 | 名称 | 说明 |
  | :--: | :-- | :--- |
  | 1 | `GND` | |
  | 2 | `BOOT` | 启动选项: 悬空 SPI 启动模式; 接地 下载启动模式 |
  | 3 | `RESET` | 重置开关: 悬空 正常使能芯片; 接地 RESET |
  | 4 | `BOOT_LOG` | 启动 boot code 打印选项 (通常无用) |
  | 5 | `GND` | |
  | 6 | `RXD0` | UART0 RX (默认用于调试) |
  | 7 | `TXD0` | UART0 TX (默认用于调试) |
  | 8 | `GND` | |
  | 9 | `TMS` | 用于 JTAG 调试 |
  | 10 | `TDI` | 用于 JTAG 调试 |
  | 11 | `TDO` | 用于 JTAG 调试 |
  | 12 | `TCK` | 用于 JTAG 调试 |
  | 13 | `GND` | |
  | 14 | `IO38` | 引出 esp32-s2 的 `IO38` |
  | 15 | `IO37` | 引出 esp32-s2 的 `IO37` |
  | 16 | `IO36` | 引出 esp32-s2 的 `IO36` |
  | 17 | `IO35` | 引出 esp32-s2 的 `IO35` |
  | 18 | `IO34` | 引出 esp32-s2 的 `IO34` |
  | 19 | `IO33` | 引出 esp32-s2 的 `IO33` |
  | 20 | `GND` | |
  | 21 | `LED1` | 引出状态指示灯 (`D2`) 控制信号 (`IO21`) |
  | 22 | `3V3` | 3.3V 电源供电 |
  | 23 | `GND` | |
  | 24 | `IO9` | 引出 esp32-s2 的 `IO9`, 复用功能: `VI` 测量 (电流传感器) |
  | 25 | `IO10` | 引出 esp32-s2 的 `IO10`, 复用功能: `VBAT` 测量 (电池电压) |
  | 26 | `IO11` | 引出 esp32-s2 的 `IO11` |
  | 27 | `IO12` | 引出 esp32-s2 的 `IO12`, 复用功能: `VBUS` 测量 (USB 供电电压) |
  | 28 | `IO13` | 引出 esp32-s2 的 `IO13`, 与 `J3` 共同引出 |
  | 29 | `IO14` | 引出 esp32-s2 的 `IO14`, 与 `J3` 共同引出 |
  | 30 | `GND` | |

## 功能电路

+ **D1** 电源指示灯 (翠绿色)

  | 项目 | 说明 |
  | :--: | :-- |
  | 功能可选 | 是 (`D1`, `R1` 不上件) |
  | 电源电压 | 3.3V |
  | LED 电流 | 20mA |

+ **D2** 状态指示灯 (冰蓝色)

  | 项目 | 说明 |
  | :--: | :-- |
  | 功能可选 | 是 (`D2`, `R2` 不上件) |
  | 电源电压 | 3.3V |
  | LED 电流 | 20mA |
  | esp32-s2 引脚 | `IO21` |
  | 接口引脚 | `LED1` (`J4` 21) |

+ **VI** 电流传感器电压检测

  | 项目 | 说明 |
  | :--: | :-- |
  | 功能可选 | 是 (`R36` 以及 `R30`, `R31`, `R32` 不上件) |
  | `VI` 量程 | 7.5V |
  | `VI` 电压缩小比例 | `3:1` |
  | `VI` 对地电阻 | 3k |
  | esp32-s2 引脚 | `IO9` |
  | 接口引脚 | `VI` (`J3` 1), `IO9` (`J4` 24) |

+ **VBAT** 电池电压检测

  | 项目 | 说明 |
  | :--: | :-- |
  | 功能可选 | 是 (`R35` 以及 `R33`, `R34` 不上件) |
  | `VBAT` 量程 | 27.5V |
  | `VBAT` 电压缩小比例 | `11:1` |
  | `VBAT` 对地电阻 | 11k |
  | esp32-s2 引脚 | `IO10` |
  | 接口引脚 | `VBAT` (`J3` 10), `IO10` (`J4` 25) |

+ **VBUS** USB 供电电压检测

  | 项目 | 说明 |
  | :--: | :-- |
  | 功能可选 | 是 (`R53` 不上件) |
  | `VBUS` 量程 | 7.5V |
  | `VBUS` 电压缩小比例 | `3:1` |
  | `VBUS` 对地电阻 | 3k |
  | esp32-s2 引脚 | `IO12` |
  | 接口引脚 | `IO12` (`J4` 27) |

+ **RESET** 芯片重置

  | 项目 | 说明 |
  | :--: | :-- |
  | 功能可选 | 是 (`R4`, `C4` 不上件) |
  | 接口引脚 | `RESET` (`J4` 3) |

## 保护电路

TODO

(2020-10-31 `v0.1`)

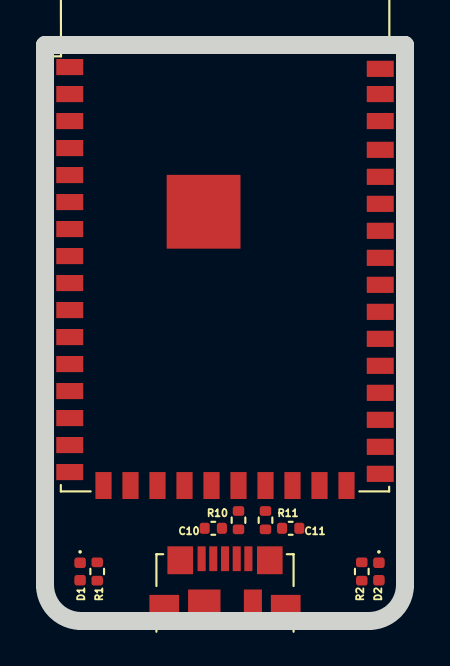
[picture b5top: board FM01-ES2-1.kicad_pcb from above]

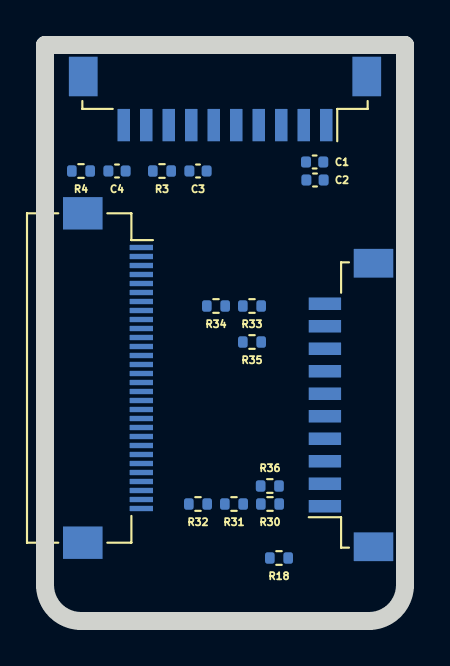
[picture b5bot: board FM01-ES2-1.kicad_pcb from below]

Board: 2 copper layers, 20.0 x 32.0 mm, 27 parts (17 on the bottom side), 48 nets, no tracks yet.

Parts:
C1: 22u; C_0402_1005Metric
C2, C3, C4: 0.1u; C_0402_1005Metric
C10, C11: 20p; C_0402_1005Metric
D1: LED-G; LED_0402_1005Metric
D2: LED-B; LED_0402_1005Metric
J1: USB_B_Micro; USB_Micro-B_Molex_47346-0001
J2, J3: Conn_01x10; Hirose_DF13C_CL535-0410-4-51_1x10-1MP_P1.25mm_Vertical
J4: Conn_01x30; Hirose_FH12-30S-0.5SH_1x30-1MP_P0.50mm_Horizontal
R1, R2: 15; R_0402_1005Metric
R3, R18, R34: 10k; R_0402_1005Metric
R4, R10, R11, R35, R36: 0; R_0402_1005Metric
R30, R31, R32, R33: 1k; R_0402_1005Metric
U1: ESP32-S2-WROVER-I; ESP32-S2-WROVER

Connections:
+3V3: C1.1, C2.1, J2.1, J4.22, R1.1, R2.1, R3.2, R18.1, U1.2
/BOOT: J4.2, U1.3
/BOOT_LOG: J4.4, U1.40
/EN: C3.2, R3.1, R4.2, U1.41
/IO1: J2.3, U1.4
/IO2: J2.4, U1.5
/IO3: J2.5, U1.6
/IO4: J2.6, U1.7
/IO5: J2.7, U1.8
/IO6: J2.8, U1.9
/IO7: J2.9, U1.10
/IO8: J2.10, U1.11
/IO9: J4.24, R36.1, U1.12
/IO10: J4.25, R35.1, U1.13
/IO11: J4.26, U1.14
/IO12: J4.27, U1.15
/IO13: J3.3, J4.28, U1.16
/IO14: J3.4, J4.29, U1.17
/IO15: J3.5, U1.18
/IO16: J3.6, U1.19
/IO17: J3.7, U1.20
/IO18: J3.8, R18.2, U1.21
/IO33: J4.19, U1.27
/IO34: J4.18, U1.28
/IO35: J4.17, U1.29
/IO36: J4.16, U1.30
/IO37: J4.15, U1.31
/IO38: J4.14, U1.32
/LED1: D2.1, J4.21, U1.24
/RESET: C4.2, J4.3, R4.1
/RXD0: J4.6, U1.38
/TCK: J4.12, U1.33
/TDI: J4.10, U1.35
/TDO: J4.11, U1.34
/TMS: J4.9, U1.36
/TXD0: J4.7, U1.37
/USB_D0+: R11.2, U1.23
/USB_D0-: R10.2, U1.22
/USB_D1+: C11.2, J1.3, R11.1
/USB_D1-: C10.1, J1.2, R10.1
/VBAT: J3.10, R34.1
/VI: J3.1, R32.1
GND: C1.2, C2.2, C3.1, C4.1, C10.2, C11.1, D1.1, J1.5, J1.6, J2.2, J3.2, J3.9, J4.1, J4.5, J4.8, J4.13, J4.20, J4.23, J4.30, R30.1, R33.2, U1.1, U1.26, U1.42, U1.43
unnamed: D1.2, R1.2
unnamed: D2.2, R2.2
unnamed: R30.2, R31.2, R36.2
unnamed: R31.1, R32.2
unnamed: R33.1, R34.2, R35.2

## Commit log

2020-09-29 init commit for fm01
2020-09-29 add doc/fm01-stage-1
2020-09-29 doc: add hardware spec
2020-09-30 doc: add price.md
2020-09-30 doc: fix typo
2020-10-01 doc: add fm02
2020-10-08 doc: add fm-series.md
2020-10-18 doc: update README.md
2020-10-18 doc: add kicad/README.md
2020-10-18 doc/kicad: add FM02-MB-1
2020-10-18 doc/kicad: FM02-MB-1 v0.1
2020-10-18 doc/kicad: update FM02-MB-1
2020-10-27 doc/kicad: add FM01-ES2-1
2020-10-27 doc/kicad: FM01-ES2-1 add PCB
2020-10-27 doc/kicad: FM01-ES2-1 update PCB
2020-10-31 doc/kicad: FM01-ES2-1 add README.md
2020-10-31 doc/kicad: FM01-ES2-1 update README.md
2020-11-01 doc: add fm01/circuit_protect.md
2020-11-03 doc/kicad: add fmesc-1-a/README.md fmesc-1-b/README.md
2020-11-03 doc/kicad: add FMESC-1-A
2020-11-05 doc/kicad: FMESC-1-A add DFN5x6_8L_EP1_P.kicad_mod
2020-11-05 doc/kicad: FMESC-1-A add PCB
2020-11-07 doc/kicad: FMESC-1-A update PCB
2020-11-07 doc/kicad: FMESC-1-A first PCB layout
2020-11-07 doc/kicad: FMESC-1-A PCB add wire (some)
2020-11-07 doc/kicad: FMESC-1-A PCB wire fail
2020-11-08 doc/kicad: add FMESC-1-C
2020-11-08 doc/kicad: FMESC-1-C add PCB
2020-11-08 doc/kicad: FMESC-1-A update PCB
2020-11-08 doc/kicad: FMESC-1-A clean PCB
2020-11-08 doc/kicad: FMESC-1-A PCB layout
2020-11-08 doc/kicad: FMESC-1-A PCB finish layout
2020-11-08 doc/kicad: FMESC-1-A PCB v0.1
2020-11-08 doc/kicad: FMESC-1-C PCB layout
2020-11-08 doc/kicad: FMESC-1-C PCB v0.1
2020-11-09 doc/kicad: FMESC-1-A PCB v0.2
2020-11-09 doc/kicad: FMESC-1-A PCB release dist/v0.2
2020-11-12 doc/kicad: update fmesc-1-a/README.md
2020-11-12 doc/kicad: add LQFP64-STM32-CLAMP
2020-11-12 doc/kicad: LQFP64-STM32-CLAMP PCB layout
2020-11-14 doc/kicad: FMESC-1-A v0.3
2020-11-14 doc/kicad: update fmesc-1-a/README.md for v0.3
2020-11-14 doc/kicad: add LQFP64-10x10mm-CLAMP
2020-11-14 doc/kicad: LQFP64-10x10mm-CLAMP PCB layout (partly)
2020-11-14 doc/kicad: LQFP64-10x10mm-CLAMP update LQFP64 3D view
2020-11-15 doc/kicad: LQFP64-10x10mm-CLAMP bottom board
2020-11-15 doc/kicad: LQFP64-10x10mm-CLAMP wire
2020-11-15 doc/kicad: LQFP64-10x10mm-CLAMP v0.1
2020-11-15 doc/kicad: FMESC-1-C update sch and clean
2020-11-15 doc/kicad: FMESC-1-C PCB wire fail (1)
2020-11-17 doc/kicad: add fm02-b-1
2020-11-17 doc/kicad: FM02-B-1 PCB border (edge.cuts)
2020-11-21 doc/kicad: lqfp64-10x10mm-clamp/README.md add test
2020-11-22 doc/kicad: LQFP64-10x10mm-CLAMP v0.1 test OK
2020-11-22 doc/kicad: FMESC-1-C PCB wire almost finish
2020-11-25 fm01/doc: update README.md
2020-11-28 doc/kicad: add FMPCBVDL-1
2020-11-28 doc/kicad: FMPCBVDL-1 v0.1
2020-11-28 doc/kicad: FMESC-1-A clean and use FMPCBVDL-1
2020-11-28 doc/kicad: FMESC-1-A v0.3 PCB
2020-11-29 doc/kicad: update README.md
2020-11-29 doc/kicad: FMESC-1-C PCB clean and use FMPCBVDL-1
2020-11-30 doc/kicad: FMESC-1-C PCB v0.2
2020-12-02 doc/kicad: FMESC-1-A PCB add center hole
2020-12-02 doc/kicad: FMESC-1-C PCB move some
2020-12-02 doc/kicad: add fmsmd-2/README.md
2020-12-03 doc/kicad: FMSMD-2 add sch
2020-12-03 doc/kicad: FMSMD-2 PCB v0.1 (1-way)
2020-12-04 doc/kicad: FMSMD-2 v0.1 PCB
2020-12-05 doc: add future.md
2020-12-08 doc/libfm-rs: add README.md
2020-12-08 doc/libfm-rs: update README.md
2020-12-08 doc/libfm-rs: README.md improve layout
2020-12-13 doc/freecad: add FMDP-3-BOX-1
2020-12-14 doc: rename
2020-12-30 doc/kicad: add FMDP-1-B
2020-12-30 doc/kicad: FMDP-1-B v0.1
2021-01-09 doc/kicad: FMDP-1-B update README.md
2021-01-17 fm01/doc/libfm-rs: update README.md
2021-02-13 update URL
2021-02-13 update DEPRECATED
2021-04-28 add fm-logo-1
2021-06-12 add lcp
